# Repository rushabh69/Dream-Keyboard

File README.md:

# My KEEB Keyboard

A 65% mechanical keyboard I'm building for [Hack Club KEEB](https://keeb.hackclub.com/), with
a rotary encoder, hotswap switches, RGB, and an OLED.

## Specs

- 65% layout with an encoder cluster (67 keys, 5×15 matrix)
- Rotary encoder (volume / page scroll), hotswap switches
- RGB lighting (SK6812) and a 128×64 OLED
- Raspberry Pi Pico (RP2040)
- RMK firmware (Rust)
- PCB designed in KiCad
- 3D-printed case, designed in Onshape

## Build

The PCB is in [`pcb/`](pcb/) (KiCad), the case in [`case/`](case/) (Onshape), and the
firmware config in [`firmware/keyboard.toml`](firmware/keyboard.toml). I'm keeping the
build log in [`JOURNAL.md`](JOURNAL.md) as I go.

## Files

- [`pcb/`](pcb/) — PCB and schematic files (KiCad), plus exported Gerbers and drill files
- [`case/`](case/) — case and plate CAD, exported as STEP/STL (mm)
- [`firmware/`](firmware/) — RMK firmware config
- [`photos/`](photos/) — build photos
- [`bom.csv`](bom.csv) — parts list
- [`JOURNAL.md`](JOURNAL.md) — build log

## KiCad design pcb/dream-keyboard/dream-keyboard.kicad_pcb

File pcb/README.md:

# PCB

KiCad project for the keyboard PCB. 65% layout with an encoder cluster, hotswap sockets,
RGB and an OLED. Raspberry Pi Pico as the controller, one 1N4148 diode per key.

Matrix: 5 rows × 15 cols. Pin mapping (matches `firmware/keyboard.toml`):

| Signal | Pico GPIO |
|---|---|
| ROW0–ROW4 | GP0–GP4 |
| COL0–COL14 | GP5–GP19 |
| Encoder A / B | GP20 / GP21 |
| RGB (WS2812 DIN) | GP22 |
| OLED SDA / SCL (I2C1) | GP26 / GP27 |

Parts / footprints to add (marbastlib for the keyboard parts):

- **Hotswap sockets** — Kailh MX hotswap footprint (marbastlib `SW_MX_1u` hotswap variant),
  not soldered switches.
- **Encoder** — EC11 rotary encoder footprint; A/B to GP20/GP21, encoder push wired into the
  matrix at (row0, col14).
- **RGB** — SK6812 MINI-E LEDs chained (DIN→DOUT), data from GP22, plus decoupling caps.
- **OLED** — 4-pin I2C header (GND/VCC/SCL/SDA) to GP27/GP26.

Switches on the 19.05 mm grid. Run DRC, then export Gerbers + drill files to `gerbers/`.

## Start from the layout (auto-place the matrix)

`layout.kle.json` is the full 65% layout with each key labelled by its `row,col` matrix
position. Instead of placing 67 keys by hand:

`dream-keyboard.net` is a pre-generated KiCad netlist for the whole matrix — all 67
switches + 67 diodes, wired to nets ROW0–ROW4 and COL0–COL14. It was generated from
`layout.kle.json` with `kle2netlist` (switch = `PCM_marbastlib-mx:SW_MX_1u`,
diode = `Diode_THT:D_DO-35_SOD27_P7.62mm_Horizontal`).

Bring the matrix into a PCB:

1. Install the **marbastlib** library so the switch footprint resolves.
2. New KiCad project in this folder → open the **PCB Editor**.
3. **File → Import → Netlist** → pick `dream-keyboard.net` → **Update PCB**. All 67
   switch+diode pairs load with the matrix already connected (you'll see the ratsnest).
4. Install the **kbplacer** plugin (Plugin and Content Manager) and run it with
   `layout.kle.json` to auto-arrange the switches on the 19.05 mm grid.
   - kbplacer: https://github.com/adamws/kbplacer
5. Hand-add the Pico, encoder, OLED header, and SK6812 chain, and wire them to the GPIO in
   the pin table above.
6. Draw the outline, route, DRC, export Gerbers.

The netlist covers only the key matrix — the Pico/encoder/OLED/RGB are added by hand.

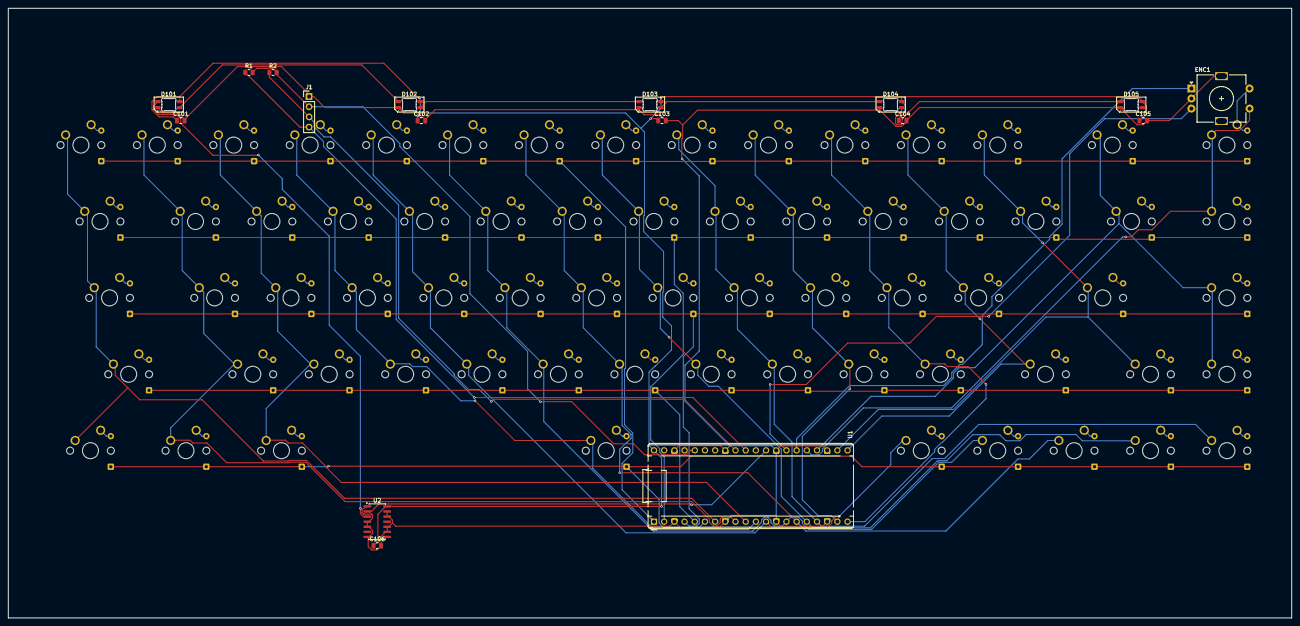
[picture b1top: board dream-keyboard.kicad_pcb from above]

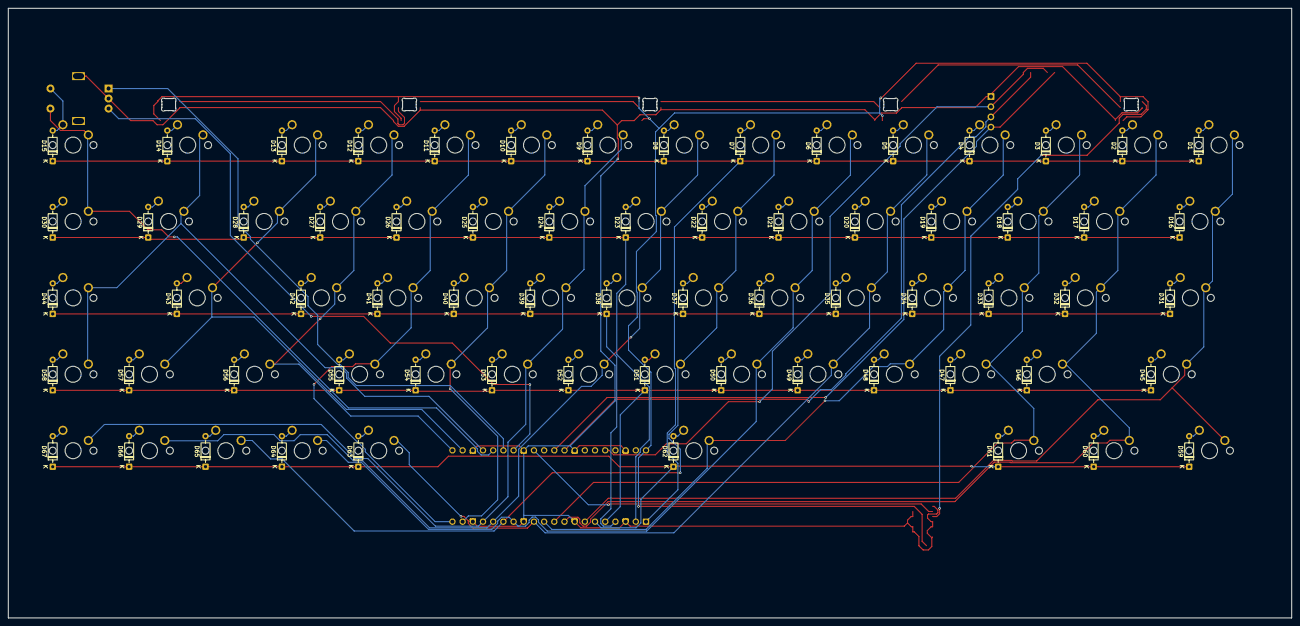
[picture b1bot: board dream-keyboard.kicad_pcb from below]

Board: 2 copper layers, 320.0 x 152.0 mm, 151 parts (67 on the bottom side), 100 nets.

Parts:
C101, C102, C103, C104, C105, C106: C_0805_2012Metric
D1, D2, D3, D4, D5, D6, D7, D8, D9, D10, D11, D12, D13, D14, D15, D16, D17, D18, D19, D20, D21, D22, D23, D24, D25, D26, D27, D28, D29, D30, D31, D32, D33, D34, D35, D36, D37, D38, D39, D40, D41, D42, D43, D44, D45, D46, D47, D48, D49, D50, D51, D52, D53, D54, D55, D56, D57, D58, D59, D60, D61, D62, D63, D64, D65, D66, D67: D; D_DO-35_SOD27_P7.62mm_Horizontal
D101, D102, D103, D104, D105: LED_SK6812MINI-E_3.2x2.8mm_P1.5mm_ReverseMount
ENC1: RotaryEncoder_Alps_EC11E-Switch_Vertical_H20mm
J1: PinHeader_1x04_P2.54mm_Vertical
R1, R2: R_0805_2012Metric
SW1, SW2, SW3, SW4, SW5, SW6, SW7, SW8, SW9, SW10, SW11, SW12, SW13, SW14, SW15, SW16, SW17, SW18, SW19, SW20, SW21, SW22, SW23, SW24, SW25, SW26, SW27, SW28, SW29, SW30, SW31, SW32, SW33, SW34, SW35, SW36, SW37, SW38, SW39, SW40, SW41, SW42, SW43, SW44, SW45, SW46, SW47, SW48, SW49, SW50, SW51, SW52, SW53, SW54, SW55, SW56, SW57, SW58, SW59, SW60, SW61, SW62, SW63, SW64, SW65, SW66, SW67: SW_Push; SW_MX_1u
U1: RaspberryPi_Pico_Common_THT
U2: SOIC-14_3.9x8.7mm_P1.27mm

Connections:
+3V3: J1.2, R1.2, R2.2, U1.36
+5V: C101.1, C102.1, C103.1, C104.1, C105.1, C106.1, D101.3, D102.3, D103.3, D104.3, D105.3, U1.40, U2.14
COL0: SW1.1, SW16.1, SW31.1, SW45.1, SW59.1, U1.7
COL1: SW2.1, SW17.1, SW32.1, SW46.1, SW60.1, U1.9
COL2: SW3.1, SW18.1, SW33.1, SW47.1, SW61.1, U1.10
COL3: SW4.1, SW19.1, SW34.1, SW48.1, SW62.1, U1.11
COL4: SW5.1, SW20.1, SW35.1, SW49.1, SW63.1, U1.12
COL5: SW6.1, SW21.1, SW36.1, SW50.1, SW64.1, U1.14
COL6: SW7.1, SW22.1, SW37.1, SW51.1, SW65.1, U1.15
COL7: SW8.1, SW23.1, SW38.1, SW52.1, SW66.1, U1.16
COL8: SW9.1, SW24.1, SW39.1, SW53.1, SW67.1, U1.17
COL9: SW10.1, SW25.1, SW40.1, SW54.1, U1.19
COL10: SW11.1, SW26.1, SW41.1, SW55.1, U1.20
COL11: SW12.1, SW27.1, SW42.1, SW56.1, U1.21
COL12: SW13.1, SW28.1, SW43.1, SW57.1, U1.22
COL13: SW14.1, SW29.1, SW44.1, SW58.1, U1.24
COL14: ENC1.S1, SW15.1, SW30.1, U1.25
ENC_A: ENC1.A, U1.26
ENC_B: ENC1.B, U1.27
GND: C101.2, C102.2, C103.2, C104.2, C105.2, C106.2, D101.1, D102.1, D103.1, D104.1, D105.1, ENC1.C, ENC1.MP, J1.1, U1.3, U1.8, U1.13, U1.18, U1.23, U1.28, U1.33, U1.38, U2.1, U2.4, U2.5, U2.7, U2.9, U2.10, U2.12, U2.13
I2C_SCL: J1.3, R2.1, U1.32
I2C_SDA: J1.4, R1.1, U1.31
LED_D0: D101.2, U2.3
LED_D1: D101.4, D102.2
LED_D2: D102.4, D103.2
LED_D3: D103.4, D104.2
LED_D4: D104.4, D105.2
unnamed: D1.2, SW1.2
unnamed: D2.2, SW2.2
unnamed: D3.2, SW3.2
unnamed: D4.2, SW4.2
unnamed: D5.2, SW5.2
unnamed: D6.2, SW6.2
unnamed: D7.2, SW7.2
unnamed: D8.2, SW8.2
unnamed: D9.2, SW9.2
unnamed: D10.2, SW10.2
unnamed: D11.2, SW11.2
unnamed: D12.2, SW12.2
unnamed: D13.2, SW13.2
unnamed: D14.2, SW14.2
unnamed: D15.2, ENC1.S2, SW15.2
unnamed: D16.2, SW16.2
unnamed: D17.2, SW17.2
unnamed: D18.2, SW18.2
unnamed: D19.2, SW19.2
unnamed: D20.2, SW20.2
unnamed: D21.2, SW21.2
unnamed: D22.2, SW22.2
unnamed: D23.2, SW23.2
unnamed: D24.2, SW24.2
unnamed: D25.2, SW25.2
unnamed: D26.2, SW26.2
unnamed: D27.2, SW27.2
unnamed: D28.2, SW28.2
unnamed: D29.2, SW29.2
unnamed: D30.2, SW30.2
unnamed: D31.2, SW31.2
unnamed: D32.2, SW32.2
unnamed: D33.2, SW33.2
unnamed: D34.2, SW34.2
unnamed: D35.2, SW35.2
unnamed: D36.2, SW36.2
unnamed: D37.2, SW37.2
unnamed: D38.2, SW38.2
unnamed: D39.2, SW39.2
unnamed: D40.2, SW40.2
unnamed: D41.2, SW41.2
unnamed: D42.2, SW42.2
unnamed: D43.2, SW43.2
unnamed: D44.2, SW44.2
unnamed: D45.2, SW45.2
unnamed: D46.2, SW46.2
unnamed: D47.2, SW47.2
unnamed: D48.2, SW48.2
unnamed: D49.2, SW49.2
unnamed: D50.2, SW50.2
unnamed: D51.2, SW51.2
unnamed: D52.2, SW52.2
unnamed: D53.2, SW53.2
unnamed: D54.2, SW54.2
unnamed: D55.2, SW55.2
unnamed: D56.2, SW56.2
unnamed: D57.2, SW57.2
unnamed: D58.2, SW58.2
unnamed: D59.2, SW59.2
unnamed: D60.2, SW60.2
unnamed: D61.2, SW61.2
unnamed: D62.2, SW62.2
unnamed: D63.2, SW63.2
unnamed: D64.2, SW64.2
unnamed: D65.2, SW65.2
unnamed: D66.2, SW66.2
unnamed: D67.2, SW67.2
RGB_IN: U1.29, U2.2
ROW0: D1.1, D2.1, D3.1, D4.1, D5.1, D6.1, D7.1, D8.1, D9.1, D10.1, D11.1, D12.1, D13.1, D14.1, D15.1, U1.1
ROW1: D16.1, D17.1, D18.1, D19.1, D20.1, D21.1, D22.1, D23.1, D24.1, D25.1, D26.1, D27.1, D28.1, D29.1, D30.1, U1.2
ROW2: D31.1, D32.1, D33.1, D34.1, D35.1, D36.1, D37.1, D38.1, D39.1, D40.1, D41.1, D42.1, D43.1, D44.1, U1.4
ROW3: D45.1, D46.1, D47.1, D48.1, D49.1, D50.1, D51.1, D52.1, D53.1, D54.1, D55.1, D56.1, D57.1, D58.1, U1.5
ROW4: D59.1, D60.1, D61.1, D62.1, D63.1, D64.1, D65.1, D66.1, D67.1, U1.6
